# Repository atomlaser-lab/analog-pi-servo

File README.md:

# Analog PI controller

## Features

   This device implementes a PI controller, with integrator
   reset. The polarity of the reset signal is selectable by choosing
   which of R11, R12 to populate.

## Layout
   PDF copies of the schmatic and PCB are found in the *Generated* folder

## Manufacture and ordering
   Gerber files are included in this repo under the directory CAM/ and under the archive CAM.zip.  Use any PCB manufacturer; a reliable and quick one out of China is JLC-PCB.

   The bill of materials can be found under the CSV text file "LaserPID.txt".  You can import this directly into Digikey.com.  The quantities are set for creating 5 boards.  You may want to add sockets for the op-amps and stand-offs for the boards when ordering.  If the INA105 is not available, you can use the INA106.

## Soldering
   All parts should be able to be soldered without much trouble.  A web-page has been created to check off parts as they are soldered.  The web-page can be created from the bill of materials (LaserPID.txt) using `python3 generate-web-page.py LaserPID.txt`.  Open the HTML file "PartList.html" in any web-browser.

## Notes
   The value of R6 and C6 should be set by the user for their particular application.  Keeping R6 as 3.3k and setting C7 as 10 nF seems to work well in controlling dipole laser powers.

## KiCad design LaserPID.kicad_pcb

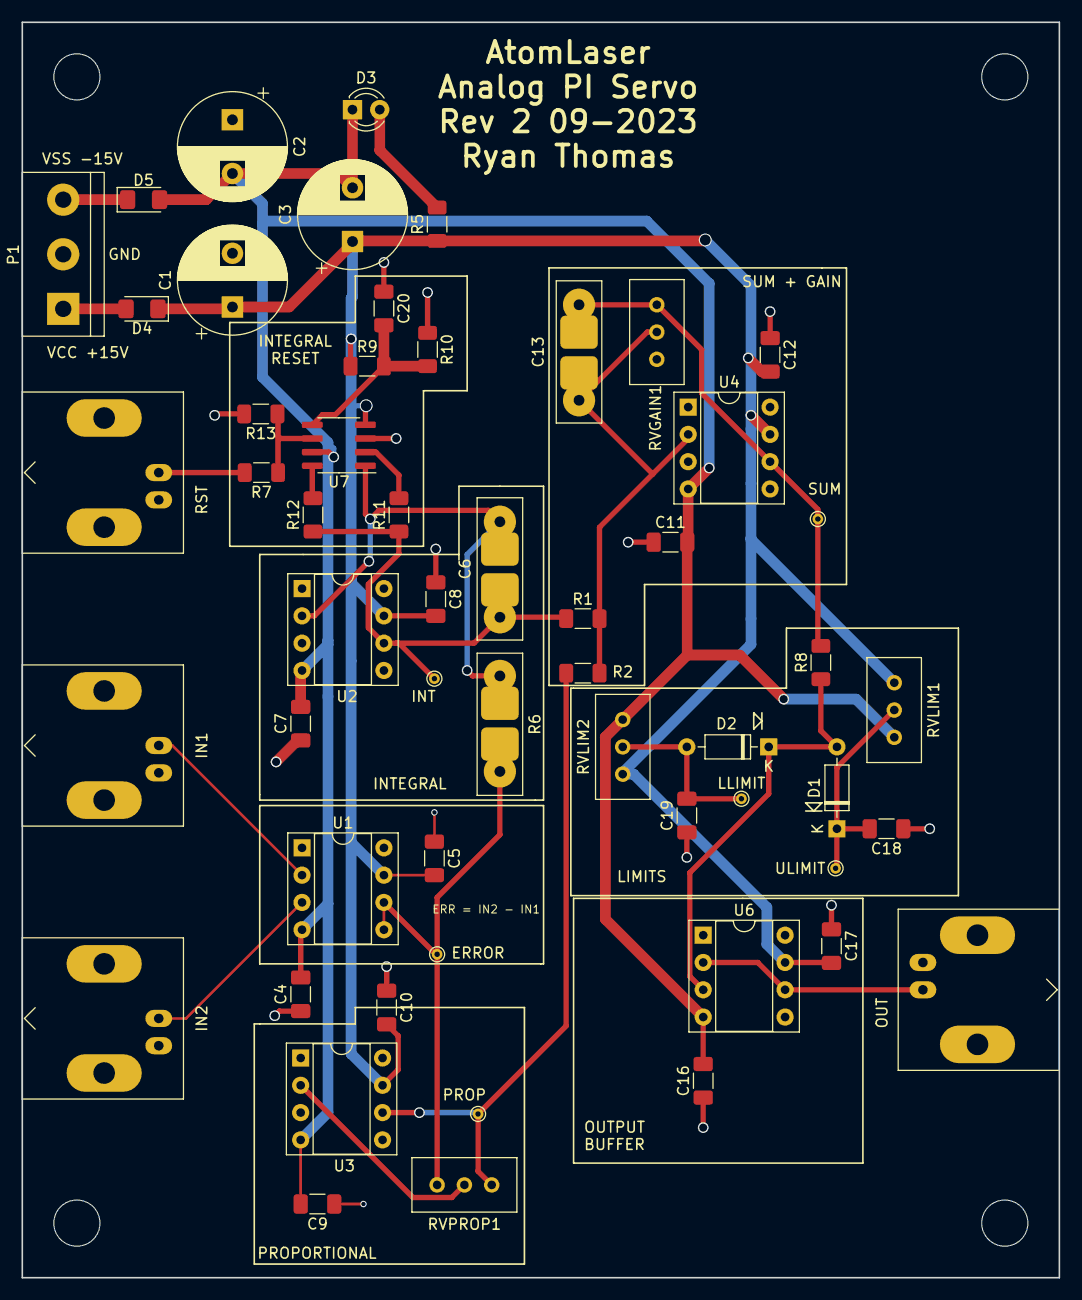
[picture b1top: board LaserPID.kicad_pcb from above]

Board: 2 copper layers, 96.5 x 116.8 mm, 55 parts (0 on the bottom side), 24 nets.

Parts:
C1, C2, C3: 100u; CP_Radial_D10.0mm_P5.00mm
C4, C5, C7, C8, C9, C10, C11, C12, C16, C17, C18, C19: 100n; C_1206_3216Metric_Pad1.33x1.80mm_HandSolder
C6: 100n; R_Universal_L13.0mm_W4.0mm_P9.00mm
C13: 10n; R_Universal_L13.0mm_W4.0mm_P9.00mm
C20: 1u; C_1206_3216Metric_Pad1.33x1.80mm_HandSolder
D1, D2: D; D_DO-35_SOD27_P7.62mm_Horizontal
D3: POWER; LED_D3.0mm
D4, D5: D; D_1206_3216Metric_Pad1.42x1.75mm_HandSolder
ERROR: ERROR; TestPoint_THTPad_D1.0mm_Drill0.5mm
IN1: IN1; BNC_Amphenol_B6252HB-NPP3G-50_Horizontal
IN2: IN2; BNC_Amphenol_B6252HB-NPP3G-50_Horizontal
INT: INT; TestPoint_THTPad_D1.0mm_Drill0.5mm
LLIMIT: LLIMIT; TestPoint_THTPad_D1.0mm_Drill0.5mm
OUT: Out; BNC_Amphenol_B6252HB-NPP3G-50_Horizontal
P1: POWER; TerminalBlock_bornier-3_P5.08mm
PROP: PROP; TestPoint_THTPad_D1.0mm_Drill0.5mm
R1, R2: 5k; R_1206_3216Metric_Pad1.30x1.75mm_HandSolder
R5: 2K7; R_1206_3216Metric_Pad1.30x1.75mm_HandSolder
R6: 3K3; R_Universal_L13.0mm_W4.0mm_P9.00mm
R7: 50; R_1206_3216Metric_Pad1.30x1.75mm_HandSolder
R8: 51K; R_1206_3216Metric_Pad1.30x1.75mm_HandSolder
R9: 20k; R_1206_3216Metric_Pad1.30x1.75mm_HandSolder
R10, R13: 10k; R_1206_3216Metric_Pad1.30x1.75mm_HandSolder
R11: 3K3; R_1206_3216Metric_Pad1.30x1.75mm_HandSolder
R12: DNP; R_1206_3216Metric_Pad1.30x1.75mm_HandSolder
RST: RST; BNC_Amphenol_B6252HB-NPP3G-50_Horizontal
RVGAIN1: 10K; Potentiometer_Bourns_3296W_Vertical
RVLIM1, RVLIM2: 10K; Potentiometer_Bourns_3296W_Vertical
RVPROP1: 10K; Potentiometer_Bourns_3296W_Vertical
SUM: SUM; TestPoint_THTPad_D1.0mm_Drill0.5mm
U1: INA105; DIP-8_W7.62mm_Socket
U2, U3, U4, U6: LM741; DIP-8_W7.62mm_Socket
U7: DG419; SOIC-8_3.9x4.9mm_P1.27mm
ULIMIT: ULIMIT; TestPoint_THTPad_D1.0mm_Drill0.5mm

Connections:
/RST: R7.1, R13.1, U7.6 (A/B)
GND: C1.2, C2.1, C4.1, C5.1, C7.1, C8.1, C9.1, C10.1, C11.1, C12.1, C16.1, C17.1, C18.1, C19.1, C20.1, IN1.2 (Ext), IN2.2 (Ext), OUT.2 (Ext), P1.2, R10.1, R13.2, RST.2 (Ext), U1.1, U2.3 (+), U3.3 (+), U4.3 (+), U7.3 (GND)
unnamed: C6.1, INT.1, R1.1, R11.1, R12.1, U2.6
unnamed: C6.2, R6.1, U2.2 (-), U7.1 (COM)
unnamed: C13.1, R1.2, R2.1, RVGAIN1.2, U4.2 (-)
unnamed: C13.2, R8.2, RVGAIN1.1, SUM.1, U4.6
unnamed: C18.2, D1.1 (K), RVLIM1.2, ULIMIT.1
unnamed: C19.2, D2.2 (A), LLIMIT.1, RVLIM2.2
unnamed: C20.2, R9.2, R10.2, U7.5 (VCC)
unnamed: D1.2 (A), D2.1 (K), R8.1, U6.3 (+)
unnamed: D3.2 (A), R5.2
unnamed: D4.2 (A), P1.1
unnamed: D5.1 (K), P1.3
unnamed: IN1.1 (In), U1.2 (-)
unnamed: IN2.1 (In), U1.3 (+)
unnamed: OUT.1 (In), U6.2 (-), U6.6
unnamed: R7.2, RST.1 (In)
unnamed: PROP.1, R2.2, RVPROP1.3, U3.6
unnamed: ERROR.1, R6.2, RVPROP1.1, U1.5, U1.6
unnamed: R11.2, U7.2 (B)
unnamed: R12.2, U7.8 (A)
unnamed: RVPROP1.2, U3.2 (-)
VCC: C1.1, C3.1, C5.2, C8.2, C10.2, C12.2, C17.2, D4.1 (K), R5.1, R9.1, RVLIM1.3, RVLIM2.3, U1.7 (V+), U2.7 (V+), U3.7 (V+), U4.7 (V+), U6.7 (V+), U7.4 (V+)
VSS: C2.2, C3.2, C4.2, C7.2, C9.2, C11.2, C16.2, D3.1 (K), D5.2 (A), RVLIM1.1, RVLIM2.1, U1.4 (V-), U2.4 (V-), U3.4 (V-), U4.4 (V-), U6.4 (V-), U7.7 (V-)

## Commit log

2016-11-14 As manufactured
2016-11-14 Fixed Readme
2016-11-14 addendum
2021-04-16 Rescued symbols, updated design, added digikey part numbers
2021-04-16 Re-made PCB with Kicad 5 foot print libraries
    Digikey part numbers now assigned
2021-06-03 Changed some part numbers, minor changes to PCB
2021-06-28 Minor updates to schematic and parts list
2021-06-28 Added gerber files
2021-08-12 Updates to board and parts list to correct some errors
2021-08-12 Added web-page for soldering, updated plots
    Added new web-page for keeping track of soldering parts on the board
    Python file generate-web-page.py uses the input text BOM to create
    the page.
    Updated generated pdf and gerber files
2023-09-12 Updated to KiCAD 6, added input protection diodes, changed filter cap footprints
2023-09-12 Updated CAM/ and Generated/
2023-09-12 Updated part list and README
